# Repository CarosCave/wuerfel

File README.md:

# wuerfel

For our open workshop day I made the following module. It's a simple 6-eyed dice with a Attiny85.

You will find the:
-  CAD-Files in the folder **KiCAD**
-  The Arduino-Sketch in the folder **Arduino**
-  The PDF documents in the folder **PDF**
-  The licence files from CERN OHL v. 1.2 under **Licence**

Or you order the complete Project by my friends from Aisler B.V.. The will deliver the complete project incl. all parts. You'll find the project under the following link: https://aisler.net/DK1CMB/workshop_kicad/wurfel

## Licence:  
**Copyright Caroline Brix 2017.**  
This documentation describes Open Hardware and is licensed under the CERN OHL v. 1.2.
You may redistribute and modify this documentation under the terms of the CERN OHL v.1.2. (http://ohwr.org/cernohl). This documentation is distributed WITHOUT ANY EXPRESS OR IMPLIED WARRANTY, INCLUDING OF MERCHANTABILITY, SATISFACTORY QUALITY AND FITNESS FOR A PARTICULAR PURPOSE. Please see the CERN OHL v.1.2 for applicable conditions

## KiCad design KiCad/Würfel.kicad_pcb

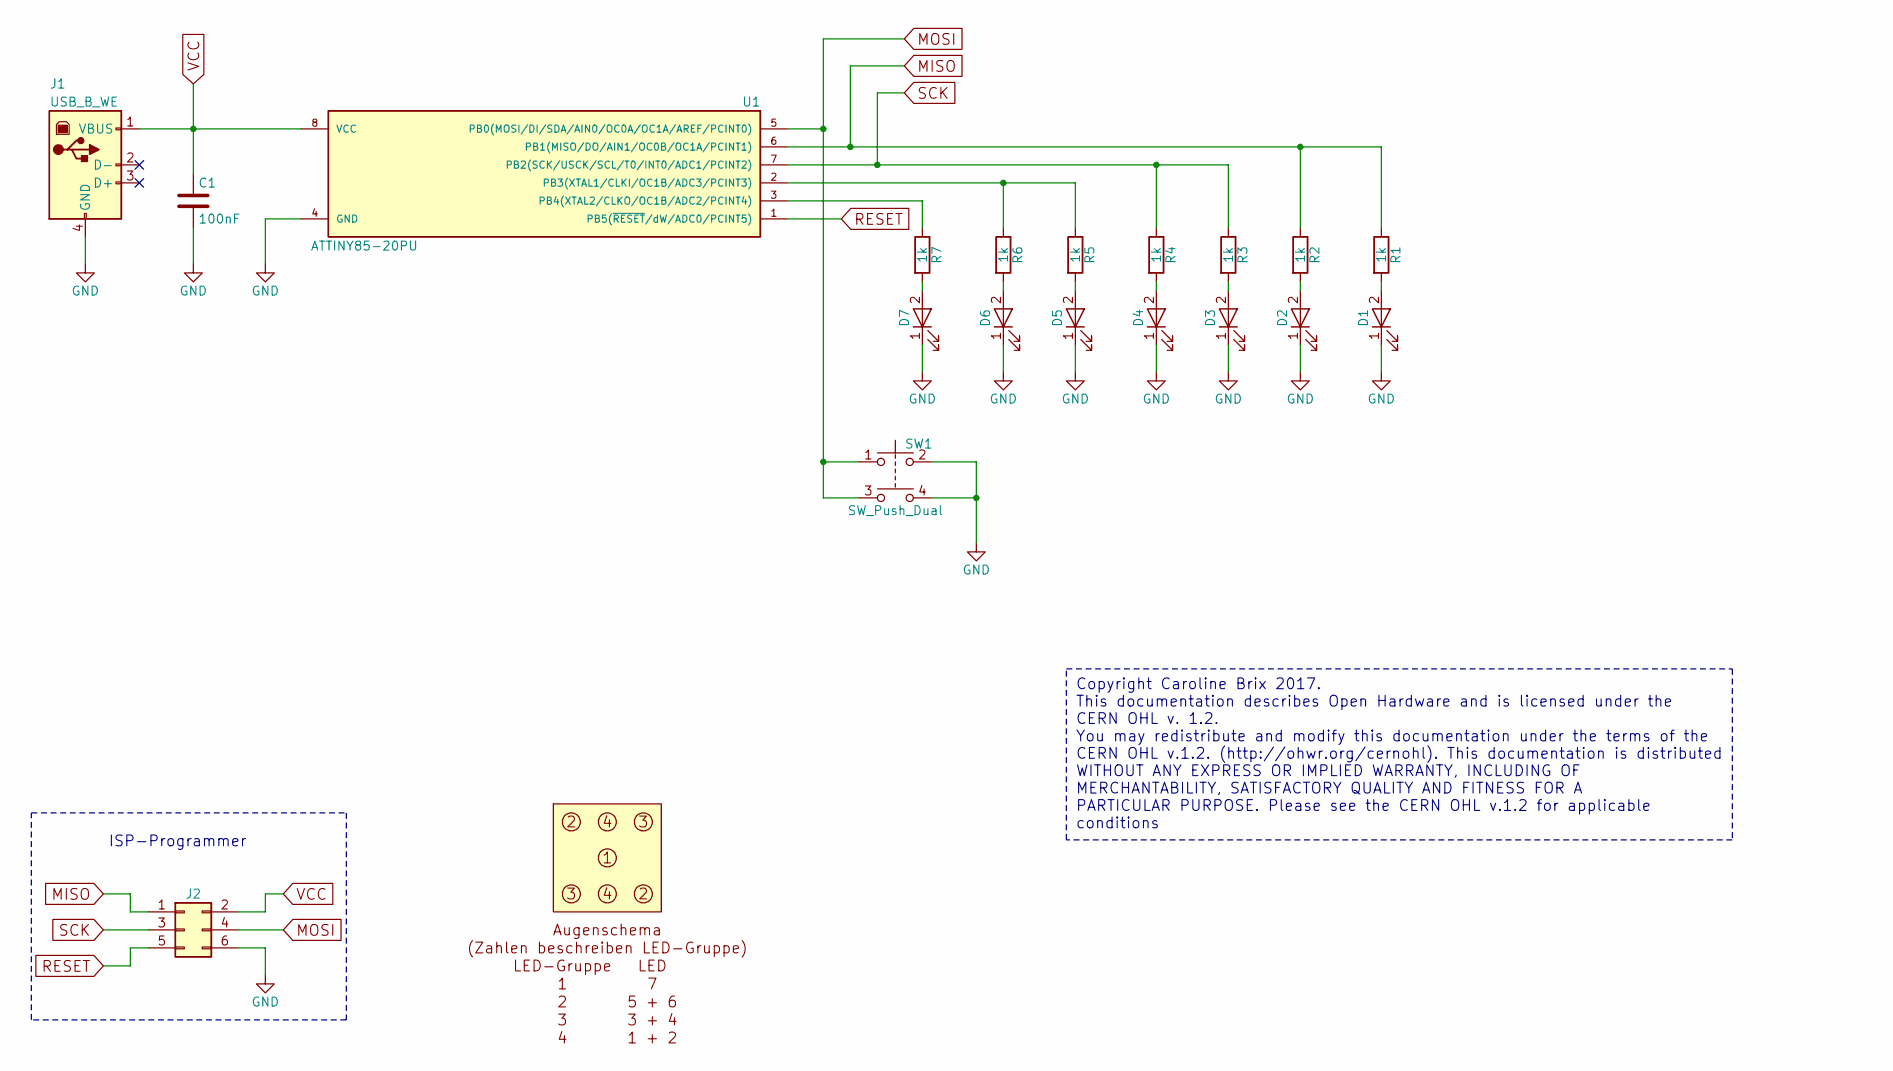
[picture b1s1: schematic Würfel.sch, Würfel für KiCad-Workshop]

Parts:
C1: 100nF; R_1206_HandSoldering
D1, D2, D3, D4, D5, D6, D7: LED; LED_D5.0mm
J1: USB_B_WE; USB_B_THT_WE
J2: Conn_02x03_Odd_Even; Pin_Header_Straight_2x03_Pitch2.54mm
R1, R2, R3, R4, R5, R6, R7: 1k; R_1206_HandSoldering
SW1: SW_Push_Dual; SW_TH_Tactile_Omron_B3F-10xx
U1: ATTINY85-20PU; DIP-8_W7.62mm
U2: Wuerfel_Bezeichner

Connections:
GND: C1.2, D1.1 (K), D2.1 (K), D3.1 (K), D4.1 (K), D5.1 (K), D6.1 (K), D7.1 (K), J1.4 (GND), J2.6, SW1.2, SW1.4, U1.4 (GND)
MISO: J2.1, R1.1, R2.1, U1.6 (PB1(MISO/DO/AIN1/OC0B/OC1A/PCINT1))
MOSI: J2.4, SW1.1, SW1.3, U1.5 (PB0(MOSI/DI/SDA/AIN0/OC0A/OC1A/AREF/PCI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)
unnamed: D1.2 (A), R1.2
unnamed: D2.2 (A), R2.2
unnamed: D3.2 (A), R3.2
unnamed: D4.2 (A), R4.2
unnamed: D5.2 (A), R5.2
unnamed: D6.2 (A), R6.2
unnamed: D7.2 (A), R7.2
unnamed: R5.1, R6.1, U1.2 (PB3(XTAL1/CLKI/OC1B/ADC3/PCINT3))
unnamed: R7.1, U1.3 (PB4(XTAL2/CLKO/OC1B/ADC2/PCINT4))
RESET: J2.5, U1.1 (PB5(~RESET~/dW/ADC0/PCINT5))
SCK: J2.3, R3.1, R4.1, U1.7 (PB2(SCK/USCK/SCL/T0/INT0/ADC1/PCINT2))
VCC: C1.1, J1.1 (VBUS), J2.2, U1.8 (VCC)

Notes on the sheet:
ISP-Programmer
Copyright Caroline Brix 2017. This documentation describes Open Hardware and is licensed under the CERN OHL v. 1.2. You may redistribute and modify this documentation under the terms of the CERN OHL v.1.2. (http://ohwr.org/cernohl). This documentation is distributed WITHOUT ANY EXPRESS OR IMPLIED W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

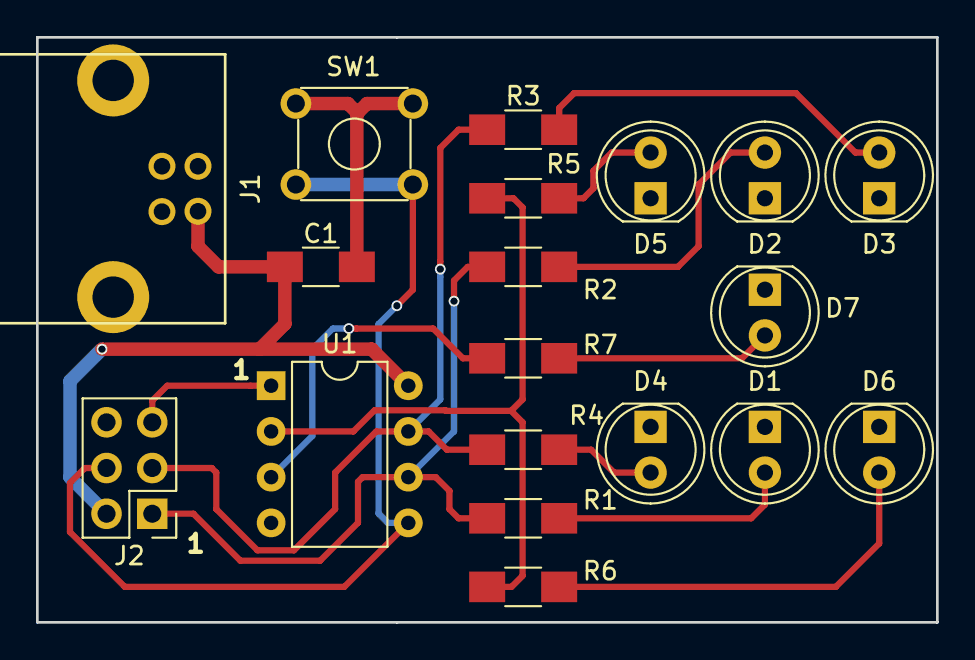
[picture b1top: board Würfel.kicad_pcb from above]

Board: 2 copper layers, 50.0 x 32.5 mm, 19 parts (0 on the bottom side), 15 nets.

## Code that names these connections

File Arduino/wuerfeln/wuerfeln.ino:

int taste = PB0;

int zahl[7][4] = {
  {LOW, LOW, LOW, LOW}, // Null
  {HIGH, LOW, LOW, LOW}, // Eins
  {LOW, HIGH, LOW, LOW}, // Zwei
  {HIGH, LOW, HIGH, LOW}, // Drei
  {LOW, HIGH, HIGH, LOW}, // Vier
  {HIGH, HIGH, HIGH, LOW}, // Fünf
  {LOW, HIGH, HIGH, HIGH} // Sechs
};


int gruppe[4] = {PB4, PB3, PB2, PB1};

int seed __attribute__ ((section (".noinit"))); // Für den Zufallsgenerator

void setup() {
  pinMode(taste, INPUT_PULLUP);

  for(uint8_t i=0; i<4; i++) {
    pinMode(gruppe[i], OUTPUT);
    digitalWrite(gruppe[i], LOW);
  }

  // Zufallsgenerator
  randomSeed(seed);
}


void zahlZeigen(uint8_t wurf) {
  if (wurf < 7) {
    for(uint8_t i=0; i<4; i++) {
      digitalWrite(gruppe[i], zahl[wurf][i]);
    }    
  }
  else {
    return;
  }
}


void loop() {
  uint8_t wurf = random(1, 7);
  uint8_t wuerfe = random(10, 100);
  int tastePush = digitalRead(taste);
  
  if(tastePush == LOW) {
    for(uint8_t i=0; i < wuerfe; i++) {   // Würfeln
      zahlZeigen(random(1, 7));
      delay(50);
    }
    zahlZeigen(0);
    delay(500);
    zahlZeigen(wurf);
    delay(500);
    zahlZeigen(0);
    delay(500);
    zahlZeigen(wurf);
    delay(2000);
    tastePush = HIGH;
    zahlZeigen(0);
  }
}

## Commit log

2017-11-12 no message
